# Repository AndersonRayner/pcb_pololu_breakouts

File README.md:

# Pololu Breakouts
A collection of breakout boards for Pololu PCBs, made with KiCAD.

To get the designs, make sure to clone recursively
```
git clone https://github.com/AndersonRayner/pololu_breakouts.git --recursive
```

As always, PRs welcome :)

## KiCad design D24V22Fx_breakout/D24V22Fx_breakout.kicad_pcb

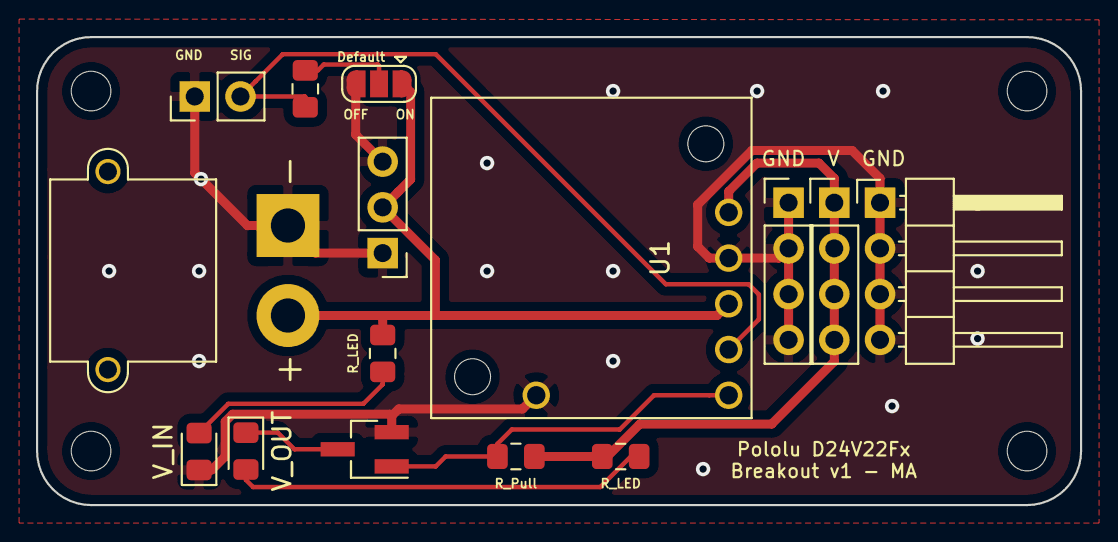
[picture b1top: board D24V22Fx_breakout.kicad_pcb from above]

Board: 2 copper layers, 58.0 x 26.0 mm, 19 parts (0 on the bottom side), 9 nets.

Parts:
D1: V_OUT; LED_0805_2012Metric_Pad1.15x1.40mm_HandSolder
D2: V_IN; LED_0805_2012Metric_Pad1.15x1.40mm_HandSolder
H1, H2, H3, H4: MountingHole; MountingHole_2.2mm_M2
J1: Conn_01x03_Male; PinHeader_1x03_P2.54mm_Vertical
J2: Conn_01x02_Male; AMASS_XT30PW-M_1x02_P2.50mm_Horizontal
J3, J4: Conn_01x03_Male; PinHeader_1x04_P2.54mm_Vertical
J5: Conn_01x03_Male; PinHeader_1x04_P2.54mm_Horizontal
J6: Conn_01x02_Male; PinHeader_1x02_P2.54mm_Vertical
JP1: Default; SolderJumper-3_P1.3mm_Open_RoundedPad1.0x1.5mm
Q1: Q_NMOS_GSD; SOT-23_Handsoldering
R1, R3: R_LED; R_0805_2012Metric_Pad1.15x1.40mm_HandSolder
R2: R_Pull; R_0805_2012Metric_Pad1.15x1.40mm_HandSolder
R4: R_DEFAULT; R_0805_2012Metric_Pad1.15x1.40mm_HandSolder
U1: Pololu_D24V22Fx; Pololu_D24V22Fx_THT

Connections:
+5V: J4.1, J4.2, J4.3, J4.4, R1.1, R2.1, U1.6
+BATT: J1.2, J2.2, JP1.1, R3.1, U1.1
EN: J6.2, R4.1, U1.2
Earth: D2.1, J1.1, J1.3, J2.1, J3.1, J3.2, J3.3, J3.4, J5.1, J5.2, J5.3, J5.4, J6.1, JP1.3, Q1.2, U1.4, U1.5
unnamed: D1.1, Q1.3
unnamed: D1.2, R1.2
unnamed: D2.2, R3.2
unnamed: JP1.2, R4.2
PG: Q1.1, R2.2, U1.3

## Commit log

2021-10-18 Update for longer thing
2021-12-29 Fixing paths
2021-12-29 submodule update
2022-10-28 Added image and pcb schematic
2022-12-04 Updated the silkscreen to include dimesnions
